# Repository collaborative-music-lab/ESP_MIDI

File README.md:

# ESP_MIDI
This repo contains hardware and software components for creating MIDI controllers using the ESP32-s3 microcontroller. The native USB port on the s3 allows for class-compliant MIDI devices which should be recognized natively by any computer.
The repo consists of:
1. **PCB**: A PCB design created in KiCad, along with PDF’s of the board and schematic
2. **Enclosure**: 3d-printable faceplates and knobs
3. **Software**: Arduino-based software for programming your MIDI controller
Each subfolder contains its own readme with additional information for each stage
# FYI / FAQS
There are several things you need to know.
### Allowing for class-compliant midi
To let ESP32-s3 appear as a class compliant device, you *must* set the ‘USB Mode’ for the board as “USB OTG(TinyUSB)”. You can find this setting in the Arduino *Tools* menu.
### Reprogramming after setting USB OTG
Once the board is set to USB OTG mode it won’t show up in Arduino as a Serial device. In order to reprogram the device you must manually hold down the ‘boot’ button on the ESP32-s3, and then press press and release the ‘reset’ on the ESP32-s3.
### Allowing for Serial debugging
In order to use serial.print debugging, you *must* set “USB CDC on boot” to “enabled”. You can find this setting in the Arduino *Tools* menu.

# Components
There are three components to this project:
1. The PCB and electronics assembly
2. The enclosure and mechanical elements
3. The firmware for the ESP-32-S3

Instructions on how to complete the project are in the readme's for these three subfolders.

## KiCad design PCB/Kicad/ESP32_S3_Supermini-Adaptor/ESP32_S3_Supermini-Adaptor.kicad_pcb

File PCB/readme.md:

# PCB and Electronics Assembly

The project consists of:

1. The main PCB, with the ESP32 pre-soldered
2. 4 potentiometers, 2 to place on the PCB and two additional off-board potentiometers with small pcbs.
3. 4 Arcade Buttons
4. An LSM6DS3 IMU breakout board
5. An RGB LED and resistors

## Assembly

Make sure get your enclosure drilled for your faceplate before you mount your PCB to the faceplate in step 9!!!

1. Place two potentiometers on the PCB. Make sure they are flat. It is a good idea to place the potentiometers on a faceplate to make sure they are aligned. Solder the potentiometers in place.
	* the potentiometers go on the opposite side of the PCB from the ESP32 (e.g. the ESP32 is on the bottom, and the potentiometers are on the top).
2. The LED uses 3 resistors with values between 120 and 470 ohm. All resistors may be the same value. Place and solder the resistors. 
3. DO NOT solder the LED yet. We will solder the PCB once we are ready to mount the electronics to the faceplate.
4. Solder the small PCBs to the two off-board potentiometers. The potentiometer pins go in the holes next to the word 'POT'
5. Solder headers to the LSM6DS3 breakout on the side that has 6 holes. Leave the five holes on the other side of the PCB empty.
6. Place the LSM6DS3 breakout into the head holes labelled 'IMU' on the PCB. Make sure the V+ and VIN pins on the PCB and breakout are aligned. Double-check - if you are not confident, ask for help! 
	* The breakout should be on the bottom of the board, the same side as the ESP32
7. Cut wires for connecting the arcade buttons and external potentiometers. You will need 3 groups with different colors:
	* 6 wires for grounds
	* 6 wires for signal
	* 2 wires for V+
8. Solder these wires into the PCB. Note that there are six places for external sensors, each with a ground, V+, and signal pad. You will need to solder each ground and signal (A1-A6) pad, but only two of the V+/3v pads. 
9. Once all of these wires are soldered in it is time to mount the PCB in the faceplate and solder the LED. 
10. Put the LED in the LED holes. The longest leg of the LED goes into the round hole next to the square hole. If you look on the bottom of the PCB you will see one trace connected to the LED holes - that hole is where the long leg goes. 
	* It is a good idea to plug in your ESP32 and test the LED works before soldering it down
	* you will also need to adjust the LED so it fits through the hold in the faceplate before soldering it.
11. Once the LED is soldered you can screw the potentiometers on the PCB to the faceplate. Use a 10mm socket to screw this down.
12. Place the arcade buttons and other potentiometers in the faceplate. Make sure the faceplate fits inside the enclosure
13. Solder the wires to the potentiometers. Look on the small PCB and you will see indications for where G, V+, and Sig go.
14. Solder wires to the Arcade buttons. These just have a ground and signal wire soldered to the two pins. It doesn't matter which pin is ground and which is signal.
15. You are done soldering! Time to program the ESP32 and test your MIDI controller. You might want to hold off on screwing the faceplate down until you have tested all of the sensors. . .

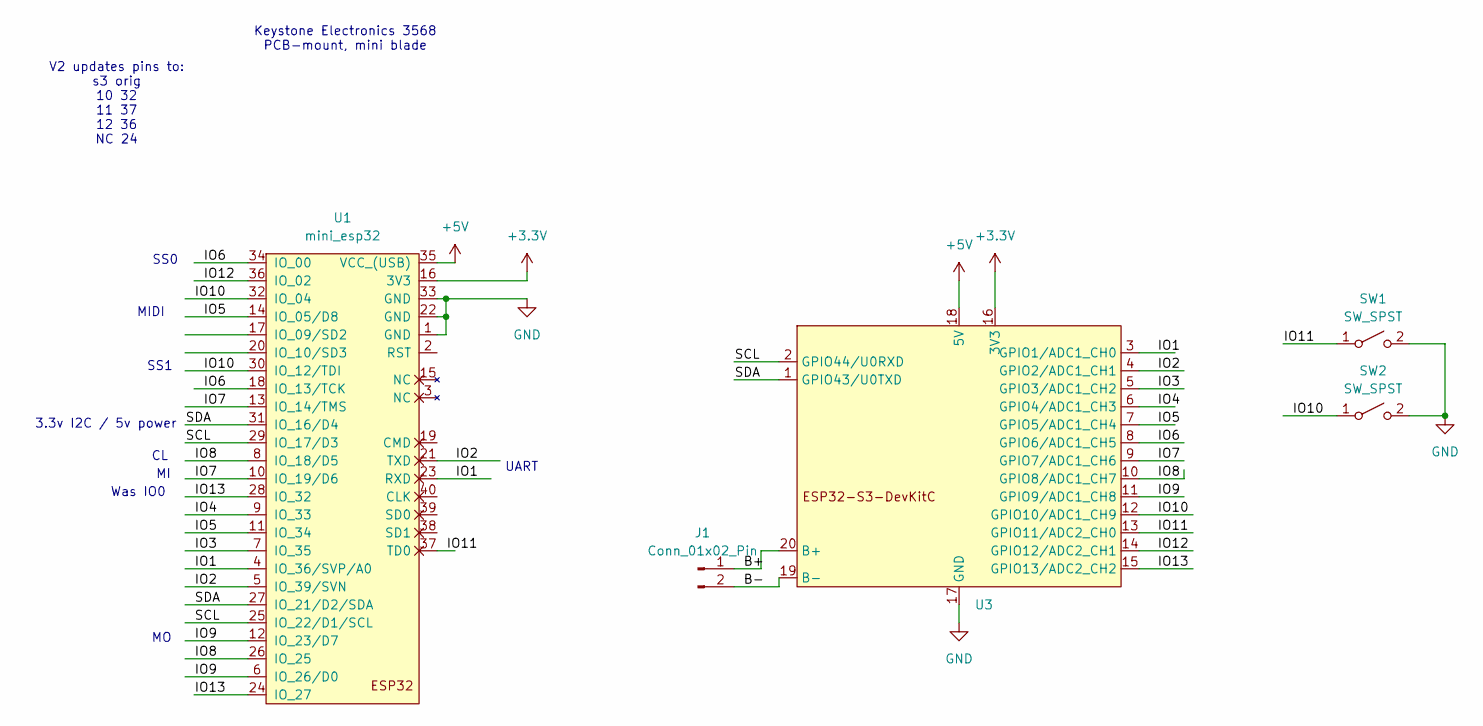
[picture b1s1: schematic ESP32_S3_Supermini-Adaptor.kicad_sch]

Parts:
J1: Conn_01x02_Pin; PinHeader_1x02_P2.54mm_Vertical
SW1, SW2: SW_SPST; SW_PUSH_6mm_H4.3mm
U1: mini_esp32; ESP32_mini
U3: ESP32S3_SUPERMINI_SHORTPADS

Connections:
+3.3V: U1.16 (3V3), U3.16 (3V3)
+5V: U1.35 (VCC_(USB)), U3.18 (5V)
/B+: J1.1, U3.20 (B+)
/B-: J1.2, U3.19 (B-)
/IO1: U1.4 (IO_36/SVP/A0), U1.23 (RXD), U3.3 (GPIO1/ADC1_CH0)
/IO2: U1.5 (IO_39/SVN), U1.21 (TXD), U3.4 (GPIO2/ADC1_CH1)
/IO3: U1.7 (IO_35), U3.5 (GPIO3/ADC1_CH2)
/IO4: U1.9 (IO_33), U3.6 (GPIO4/ADC1_CH3)
/IO5: U1.11 (IO_34), U1.14 (IO_05/D8), U3.7 (GPIO5/ADC1_CH4)
/IO6: U1.18 (IO_13/TCK), U1.34 (IO_00), U3.8 (GPIO6/ADC1_CH5)
/IO7: U1.10 (IO_19/D6), U1.13 (IO_14/TMS), U3.9 (GPIO7/ADC1_CH6)
/IO8: U1.8 (IO_18/D5), U1.26 (IO_25), U3.10 (GPIO8/ADC1_CH7)
/IO9: U1.6 (IO_26/D0), U1.12 (IO_23/D7), U3.11 (GPIO9/ADC1_CH8)
/IO10: SW2.1 (A), U1.30 (IO_12/TDI), U1.32 (IO_04), U3.12 (GPIO10/ADC1_CH9)
/IO11: SW1.1 (A), U1.37 (TD0), U3.13 (GPIO11/ADC2_CH0)
/IO12: U1.36 (IO_02), U3.14 (GPIO12/ADC2_CH1)
/IO13: U1.24 (IO_27), U1.28 (IO_32), U3.15 (GPIO13/ADC2_CH2)
/SCL: U1.25 (IO_22/D1/SCL), U1.29 (IO_17/D3), U3.2 (GPIO44/U0RXD)
/SDA: U1.27 (IO_21/D2/SDA), U1.31 (IO_16/D4), U3.1 (GPIO43/U0TXD)
GND: SW1.2 (B), SW2.2 (B), U1.1 (GND), U1.22 (GND), U1.33 (GND), U3.17 (GND)

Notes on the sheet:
MIDI
3.3v I2C / 5v power
SS0
UART
Was IO0
SS1
V2 updates pins to: s3 orig 10 32 11 37 12 36 NC 24
Keystone Electronics 3568 PCB-mount, mini blade

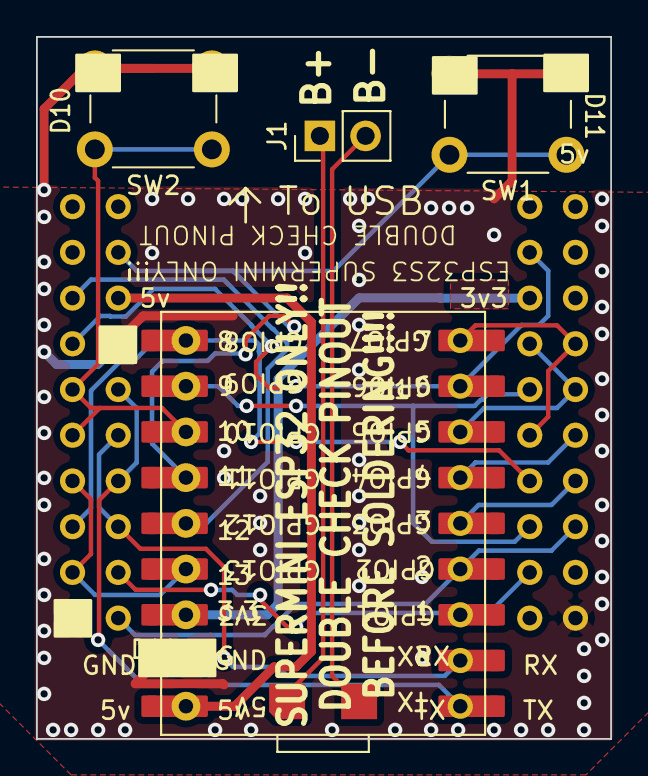
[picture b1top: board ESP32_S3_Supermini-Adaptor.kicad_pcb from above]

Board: 2 copper layers, 31.9 x 39.0 mm, 5 parts (0 on the bottom side), 20 nets.

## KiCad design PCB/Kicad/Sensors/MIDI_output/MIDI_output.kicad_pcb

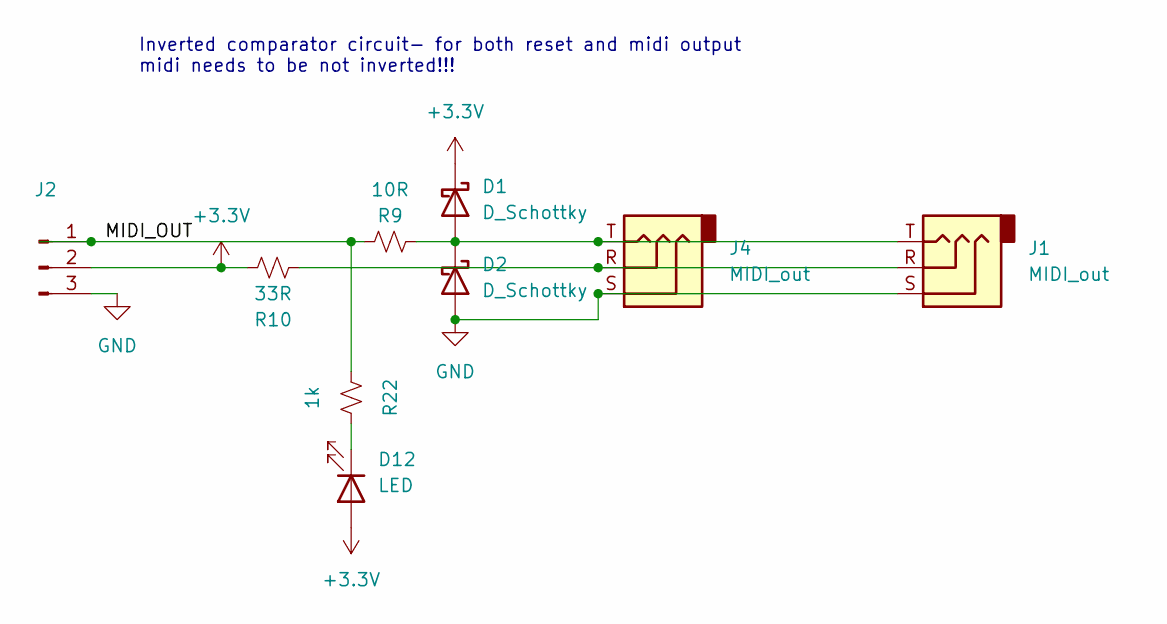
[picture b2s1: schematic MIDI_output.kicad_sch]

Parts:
D1, D2: D_Schottky; D_A-405_P10.16mm_Horizontal
D12: LED; LED_D3.0mm
J1: MIDI_out; Jack_3.5mm_QingPu_WQP-PJ398SM_Vertical_CircularHoles_1
J2: Conn_01x03_Pin; PinHeader_1x03_P2.54mm_Vertical
J4: MIDI_out; Jack_3.5mm_Ledino_KB3SPRS_Horizontal
R9: 10R; R_Axial_DIN0411_L9.9mm_D3.6mm_P15.24mm_Horizontal
R10: 33R; R_Axial_DIN0411_L9.9mm_D3.6mm_P15.24mm_Horizontal
R22: 1k; R_Axial_DIN0411_L9.9mm_D3.6mm_P15.24mm_Horizontal

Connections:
+3.3V: D1.1 (K), D12.2 (A), J2.2, R10.1
/MIDI_OUT: J2.1, R9.1, R22.1
GND: D2.2 (A), J1.S, J2.3, J4.S
unnamed: D1.2 (A), D2.1 (K), J1.T, J4.T, R9.2
unnamed: D12.1 (K), R22.2
unnamed: J1.R, J4.R, R10.2

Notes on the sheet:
Inverted comparator circuit- for both reset and midi output midi needs to be not inverted!!!

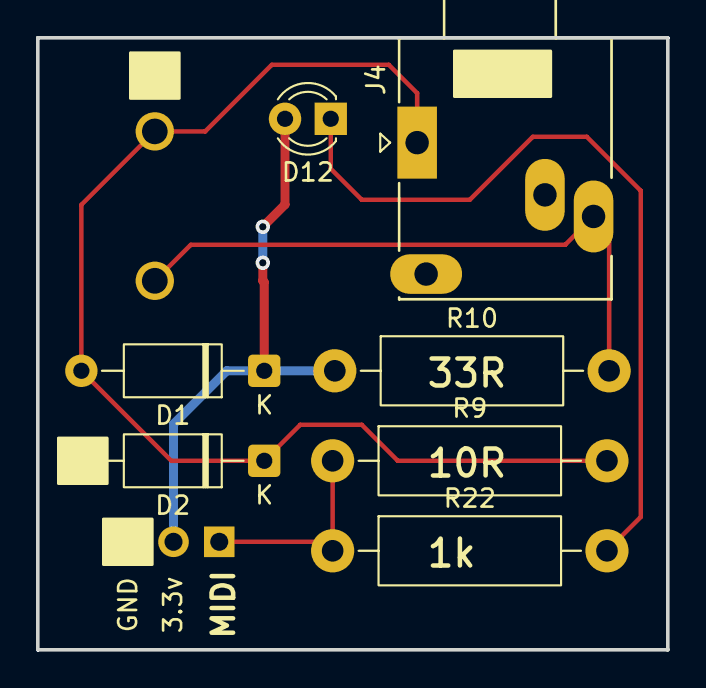
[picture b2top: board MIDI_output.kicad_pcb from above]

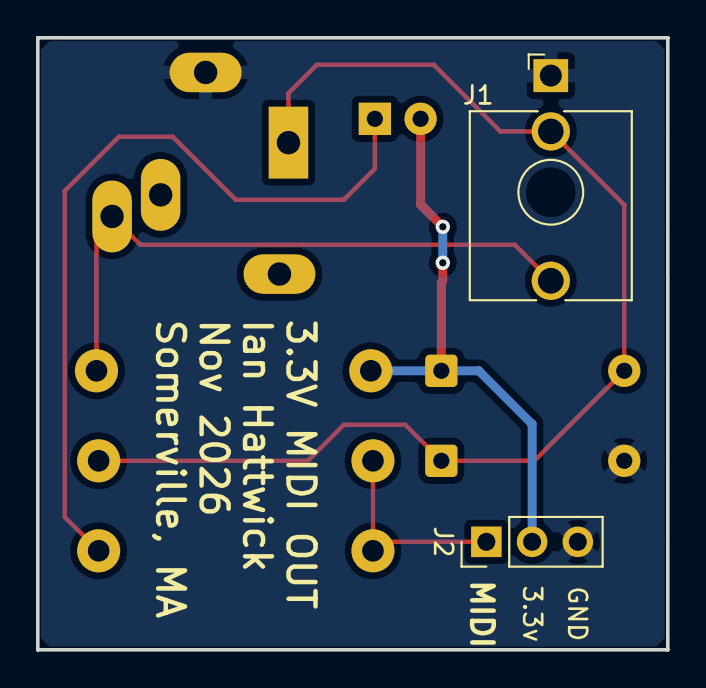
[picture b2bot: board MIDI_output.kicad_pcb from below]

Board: 2 copper layers, 35.0 x 34.0 mm, 9 parts (2 on the bottom side), 6 nets.

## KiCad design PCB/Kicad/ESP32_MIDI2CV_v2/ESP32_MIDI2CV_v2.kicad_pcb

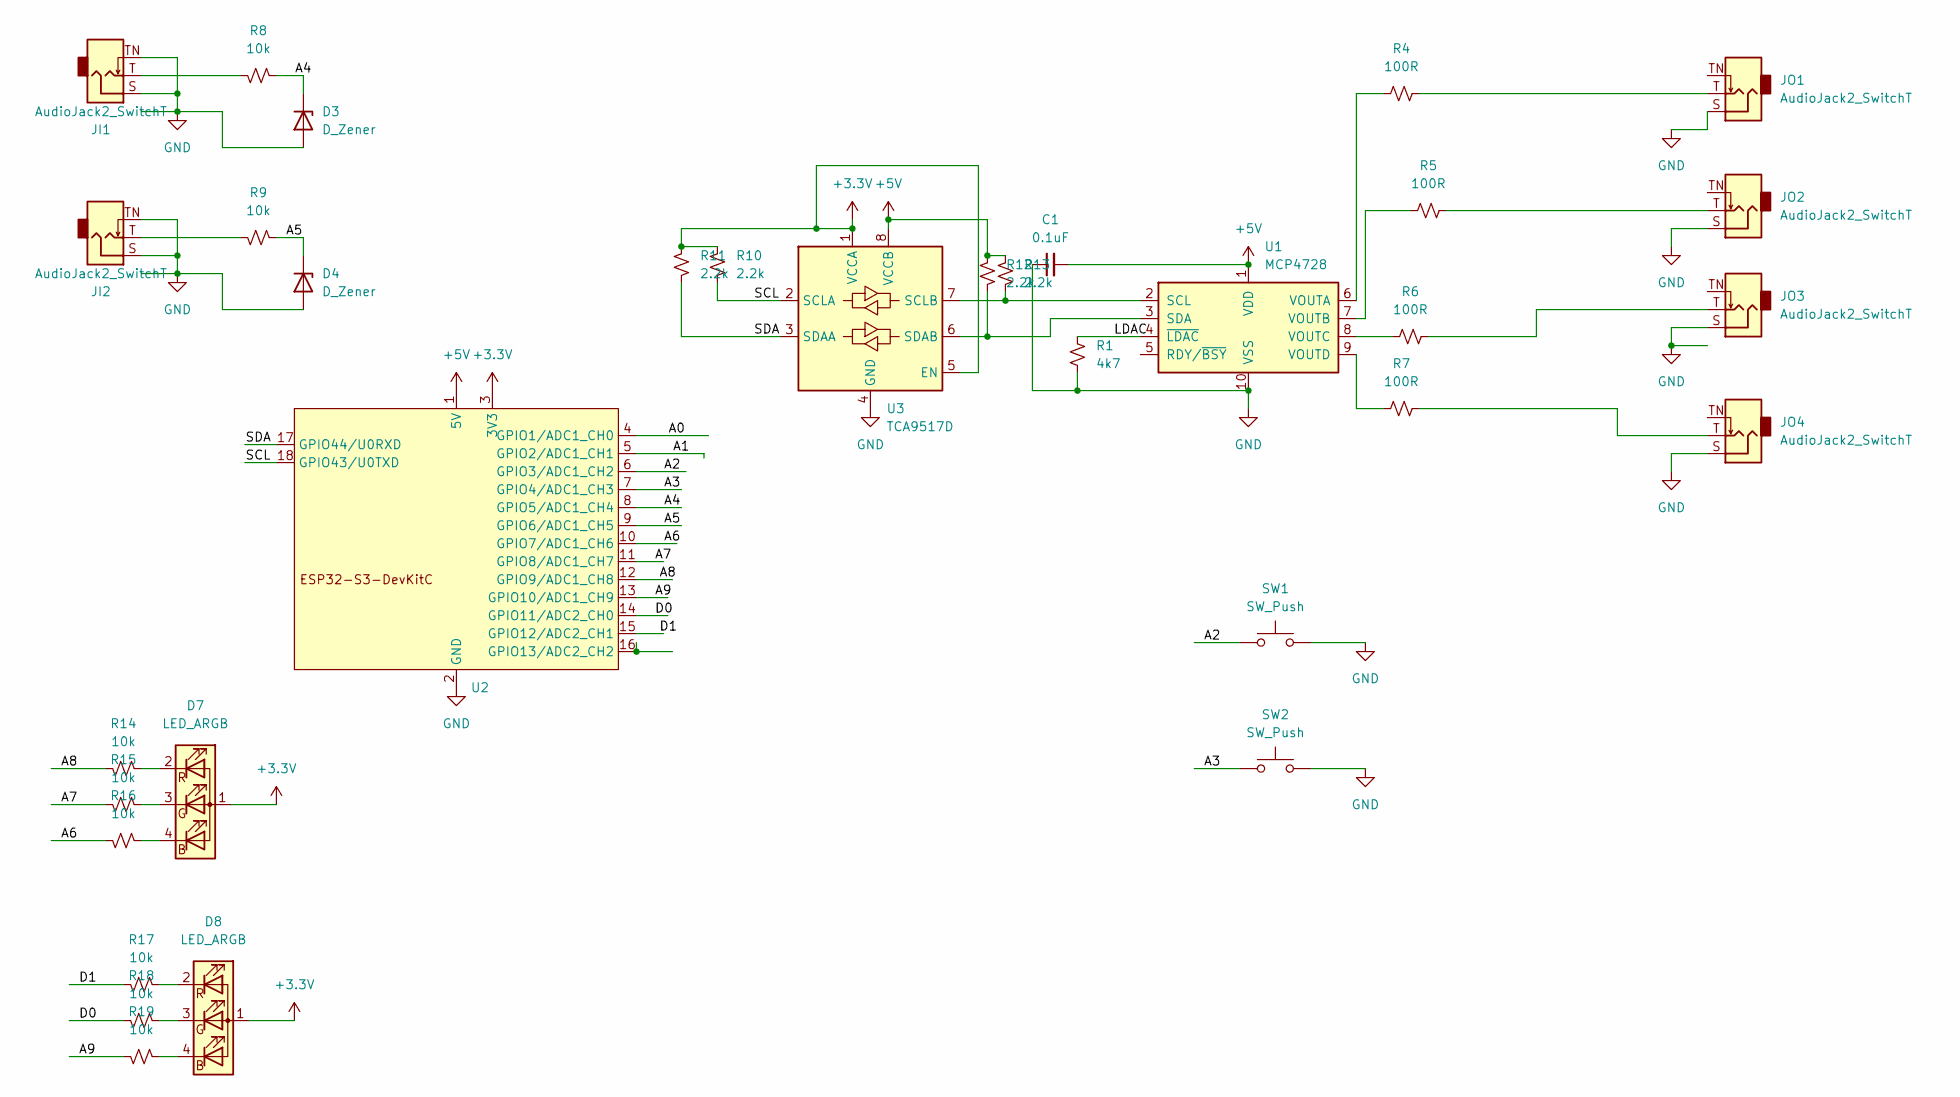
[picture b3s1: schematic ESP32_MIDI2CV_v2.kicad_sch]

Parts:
C1: 0.1uF; C_0805_2012Metric_Pad1.18x1.45mm_HandSolder
D3, D4: D_Zener; D_DO-35_SOD27_P7.62mm_Horizontal
D7, D8: LED_ARGB; LED_D5.0mm-4_RGB_Wide_Pins
JI1, JI2: AudioJack2_SwitchT; Jack_3.5mm_QingPu_WQP-PJ398SM_Vertical_CircularHoles
JO1, JO2, JO3, JO4: AudioJack2_SwitchT; Jack_3.5mm_QingPu_WQP-PJ398SM_Vertical_CircularHoles
R1: 4k7; R_0805_2012Metric
R4, R5, R6, R7: 100R; R_0805_2012Metric
R8, R9, R14, R15, R16, R17, R18, R19: 10k; R_0805_2012Metric
R10, R11, R12, R13: 2.2k; R_0805_2012Metric
SW1, SW2: SW_Push; SW_PUSH_6mm_H5mm
U1: MCP4728; MSOP-10_3x3mm_P0.5mm
U2: Wifiduino-ESP32S3-SMD
U3: TCA9517D; SOIC-8_3.9x4.9mm_P1.27mm

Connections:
+3.3V: D7.1 (A), D8.1 (A), R10.1, R11.1, U2.3 (3V3), U3.1 (VCCA), U3.5 (EN)
+5V: C1.2, R12.1, R13.1, U1.1 (VDD), U2.1 (5V), U3.8 (VCCB)
/A0: U2.4 (GPIO1/ADC1_CH0)
/A1: U2.5 (GPIO2/ADC1_CH1)
/A2: SW1.2, U2.6 (GPIO3/ADC1_CH2)
/A3: SW2.2, U2.7 (GPIO4/ADC1_CH3)
/A4: D3.1 (K), R8.1, U2.8 (GPIO5/ADC1_CH4)
/A5: D4.1 (K), R9.1, U2.9 (GPIO6/ADC1_CH5)
/A6: R16.2, U2.10 (GPIO7/ADC1_CH6)
/A7: R15.2, U2.11 (GPIO8/ADC1_CH7)
/A8: R14.2, U2.12 (GPIO9/ADC1_CH8)
/A9: R19.2, U2.13 (GPIO10/ADC1_CH9)
/D0: R18.2, U2.14 (GPIO11/ADC2_CH0)
/D1: R17.2, U2.15 (GPIO12/ADC2_CH1)
/LDAC: R1.1, U1.4 (~LDAC)
/SCL: R10.2, U2.18 (GPIO43/U0TXD), U3.2 (SCLA)
/SDA: R11.2, U2.17 (GPIO44/U0RXD), U3.3 (SDAA)
GND: C1.1, D3.2 (A), D4.2 (A), JI1.S, JI1.TN, JI2.S, JI2.TN, JO1.S, JO2.S, JO3.S, JO4.S, R1.2, SW1.1, SW2.1, U1.10 (VSS), U2.2 (GND), U3.4 (GND)
unnamed: D7.4 (BK), R16.1
unnamed: D7.3 (GK), R15.1
unnamed: D7.2 (RK), R14.1
unnamed: D8.4 (BK), R19.1
unnamed: D8.3 (GK), R18.1
unnamed: D8.2 (RK), R17.1
unnamed: JI1.T, R8.2
unnamed: JI2.T, R9.2
unnamed: JO1.T, R4.2
unnamed: JO2.T, R5.2
unnamed: JO3.T, R6.2
unnamed: JO4.T, R7.2
unnamed: R13.2, U1.2 (SCL), U3.7 (SCLB)
unnamed: R12.2, U1.3 (SDA), U3.6 (SDAB)
unnamed: R4.1, U1.6 (VOUTA)
unnamed: R5.1, U1.7 (VOUTB)
unnamed: R6.1, U1.8 (VOUTC)
unnamed: R7.1, U1.9 (VOUTD)

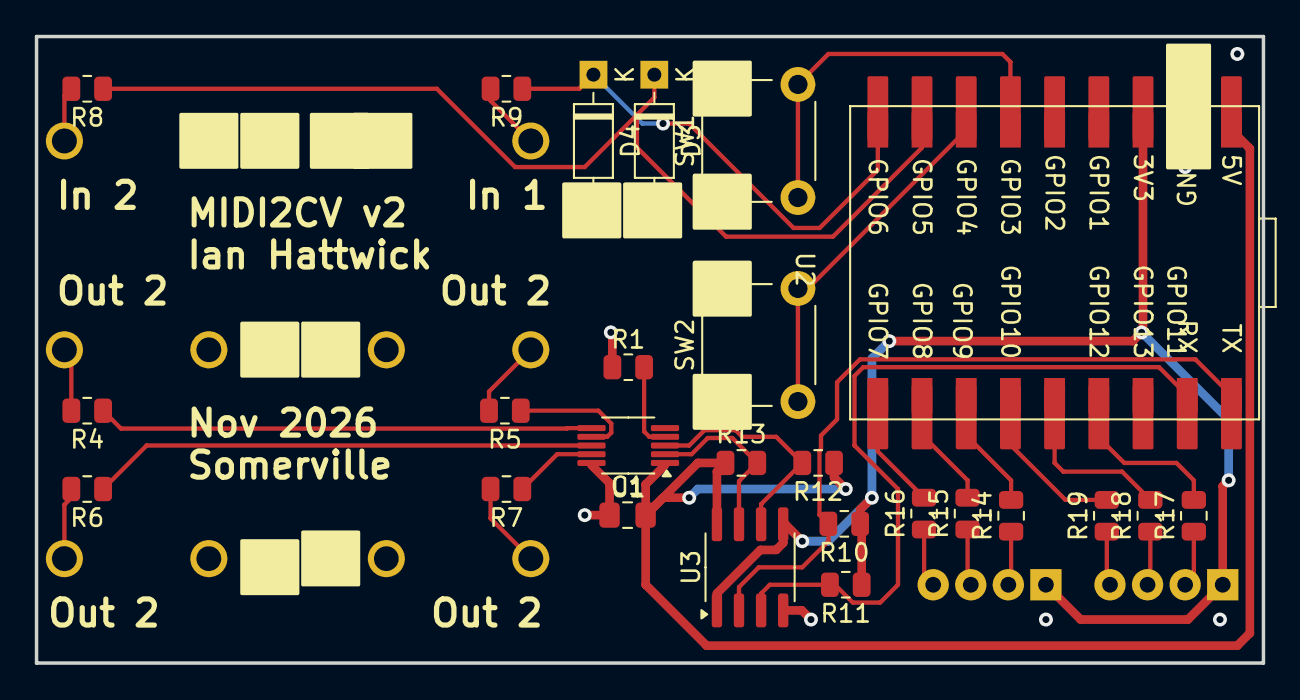
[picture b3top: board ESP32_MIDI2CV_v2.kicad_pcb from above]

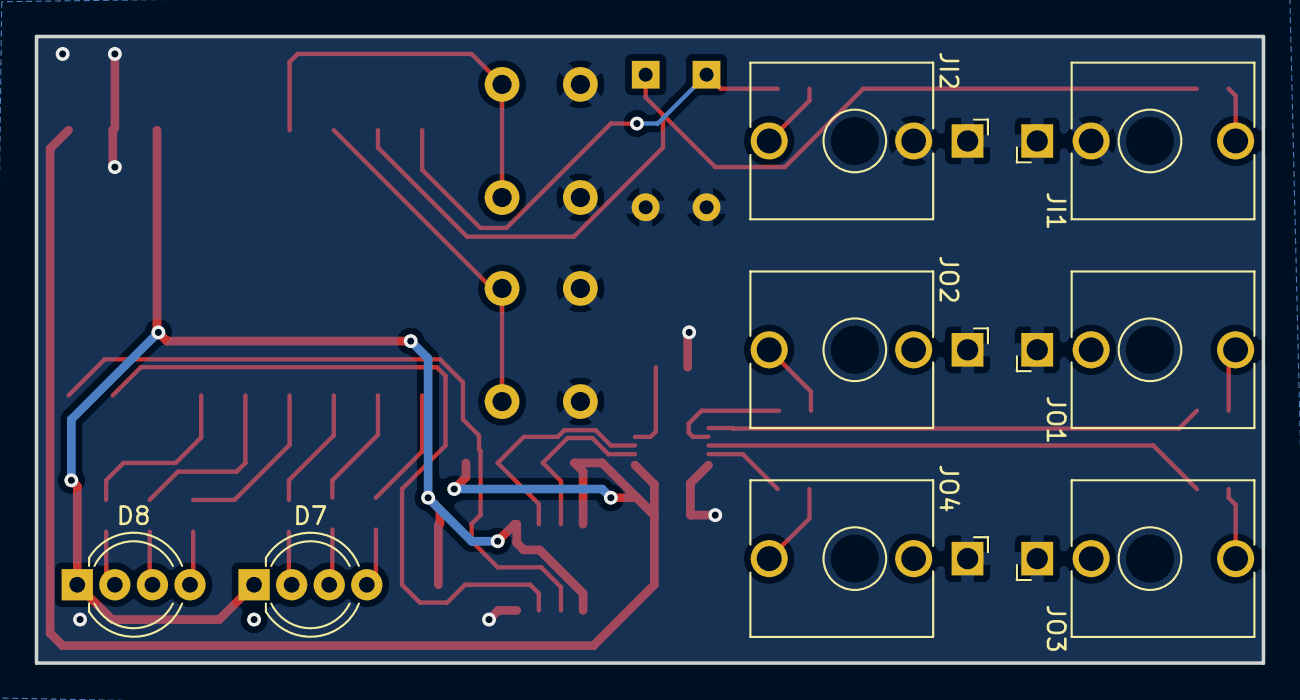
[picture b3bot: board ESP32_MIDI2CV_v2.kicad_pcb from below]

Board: 2 copper layers, 70.5 x 36.0 mm, 33 parts (8 on the bottom side), 34 nets.

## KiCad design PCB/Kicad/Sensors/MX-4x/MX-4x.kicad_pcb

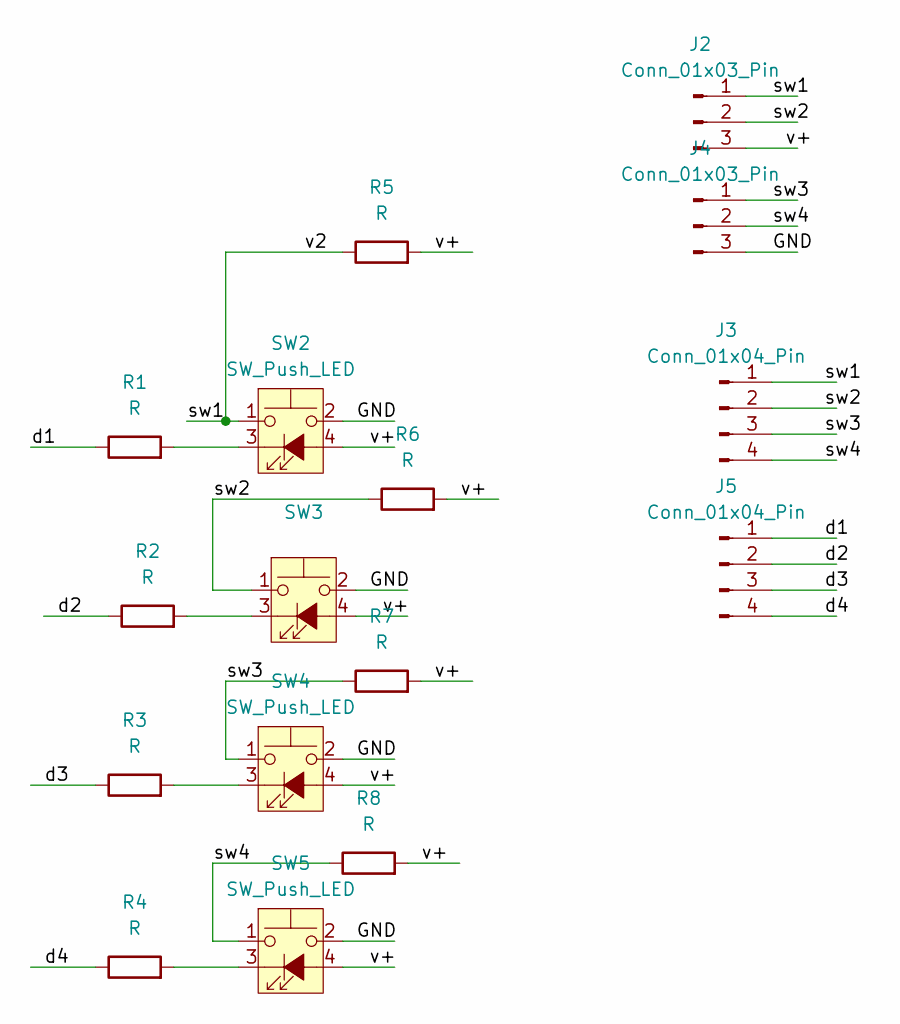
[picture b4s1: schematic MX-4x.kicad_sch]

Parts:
J2, J4: Conn_01x03_Pin; PinHeader_1x03_P2.54mm_Vertical
J3, J5: Conn_01x04_Pin; PinHeader_1x04_P2.54mm_Vertical
R1, R2, R3, R4, R5, R6, R7, R8: R; R_Axial_DIN0207_L6.3mm_D2.5mm_P2.54mm_Vertical
SW2, SW3, SW4, SW5: SW_Push_LED; MXOnly-1U

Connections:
/GND: J4.3, SW2.2, SW3.2, SW4.2, SW5.2
/d1: J5.1, R1.1
/d2: J5.2, R2.1
/d3: J5.3, R3.1
/d4: J5.4, R4.1
/sw1: J2.1, J3.1, R5.1, SW2.1
/sw2: J2.2, J3.2, R6.1, SW3.1
/sw3: J3.3, J4.1, R7.1, SW4.1
/sw4: J3.4, J4.2, R8.1, SW5.1
/v+: J2.3, R5.2, R6.2, R7.2, R8.2, SW2.4 (A), SW3.4 (A), SW4.4 (A), SW5.4 (A)
unnamed: R1.2, SW2.3 (K)
unnamed: R2.2, SW3.3 (K)
unnamed: R3.2, SW4.3 (K)
unnamed: R4.2, SW5.3 (K)

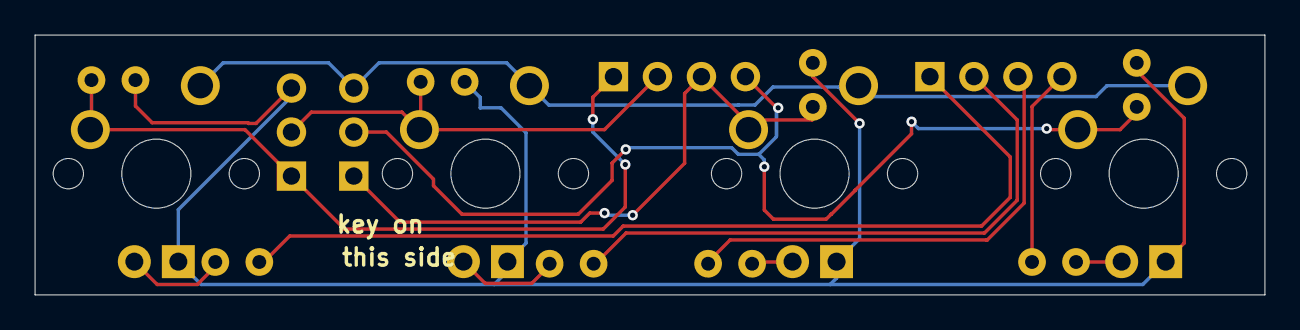
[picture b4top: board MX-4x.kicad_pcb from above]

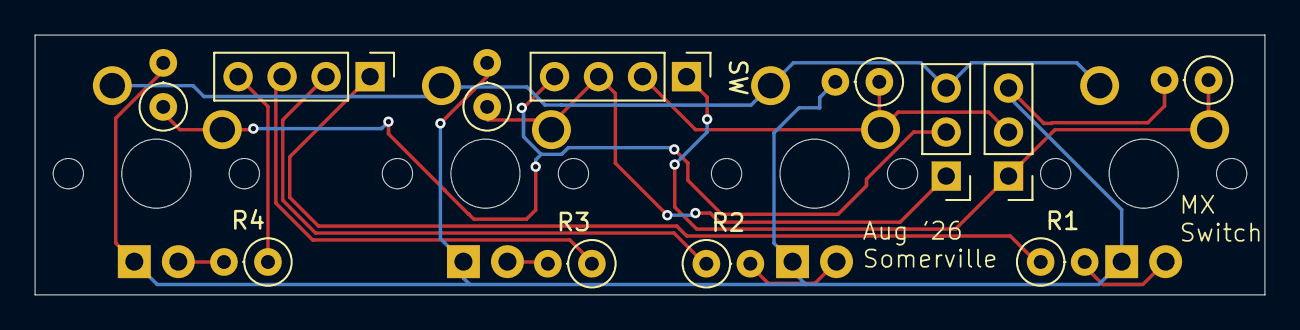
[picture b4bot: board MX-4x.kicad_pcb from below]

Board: 2 copper layers, 71.0 x 15.0 mm, 16 parts (12 on the bottom side), 14 nets.

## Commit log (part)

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2024-06-20 initial gerbers
2024-06-27 Create analogRead test sketch
2024-06-27 update simple_midi_imu
2024-06-27 update PCBs
2024-07-09 adding v2 PCB
2024-07-09 Adding simple IMU sketches
2024-07-09 update folder structure
2024-07-09 Added enclosure elements
2024-07-09 Update PCB files
2024-07-11 update firmware and faceplates
2024-07-11 Create readme.md
    To Do:
    - add link for Arduino installer
    - add link for esp32 definition
2024-07-15 Updating enclosures
2024-07-15 adding readmes
2024-07-15 remove redundant firmware
2024-07-15 session 1 notes
2024-07-16 limit sending IMU data
2024-07-16 added web audio examples
2024-07-16 fix scope
2024-12-20 Jan 24 v1
2025-01-10 Jan 10 commit - up to v4
2025-01-13 kicad refresh
2025-01-14 added v5
2025-01-19 added v6 with new USBMIDI
2025-01-20 Switched to new library and added LED midi messages
2025-01-21 update v6
2025-01-21 getting up to date
2025-01-24 Added back led responsiveness on startup
2025-06-22 firmware
2025-06-30 added wand and barre
2025-07-03 update all kicad designs for week 1
2025-07-11 files Jul 10
2025-07-13 semifinal code for summer25
2025-07-14 final wand
2025-07-14 final firmware
2025-07-16 wand v2_1
2025-07-23 added touch v1_1
2025-07-27 July 26 gerbers
2025-07-31 tweaking capsense settings and imu values
2025-08-02 Robin v2 with binary
2025-08-03 added support for BMI160
2025-08-05 adding midi buffering
2025-09-01 add USB device name
2025-09-01 robin and strip PCB updates
2025-09-01 Add strip firmware
2026-02-26 lots of pcb updates!
2026-06-07 created instruments
2026-06-08 robin
2026-06-09 robin aulos
2026-06-10 aulos
2026-06-12 default dac mbira
2026-06-12 esp-now class
2026-06-17 esp-now and robin
2026-06-17 espmidi2cv_v2
2026-06-17 mbira
2026-06-17 robin and midi handler
2026-06-23 new trigger algorithm
2026-06-25 robin updates
